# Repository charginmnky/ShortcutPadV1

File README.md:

# ShortcutPadV1
Shortcut PCB for desktop shortcuts like macros, muting, and volume controls.
## Pathfinder Session 1 - [40 minutes]
What I did:
I installed KiCad and Wakatime, and made my hackatime account.

Screenshot of progress:

## Pathfinder Session 2 - [40 minutes]
What I did:
I created my schematic, with 4 buttons and 4 leds.

Screenshot of progress:

## Pathfinder Session 3 - [2 hours 40 minutes]
What I did:
I added my footprints, and wired & designed my pcb.

Screenshot of progress:

## Pathfinder Session 4 - [20 minutes]
What I did:
I added 3d models of the parts to my code.

Screenshot of progress:

## Pathfinder Session 5 - [10 minutes]
What I did:
I started my code in arduino IDE.

Screenshot of progress:

## Pathfinder Session 6 - [30 minutes]
What I did:
I finished my code in arduino IDE.

Screenshot of progress:

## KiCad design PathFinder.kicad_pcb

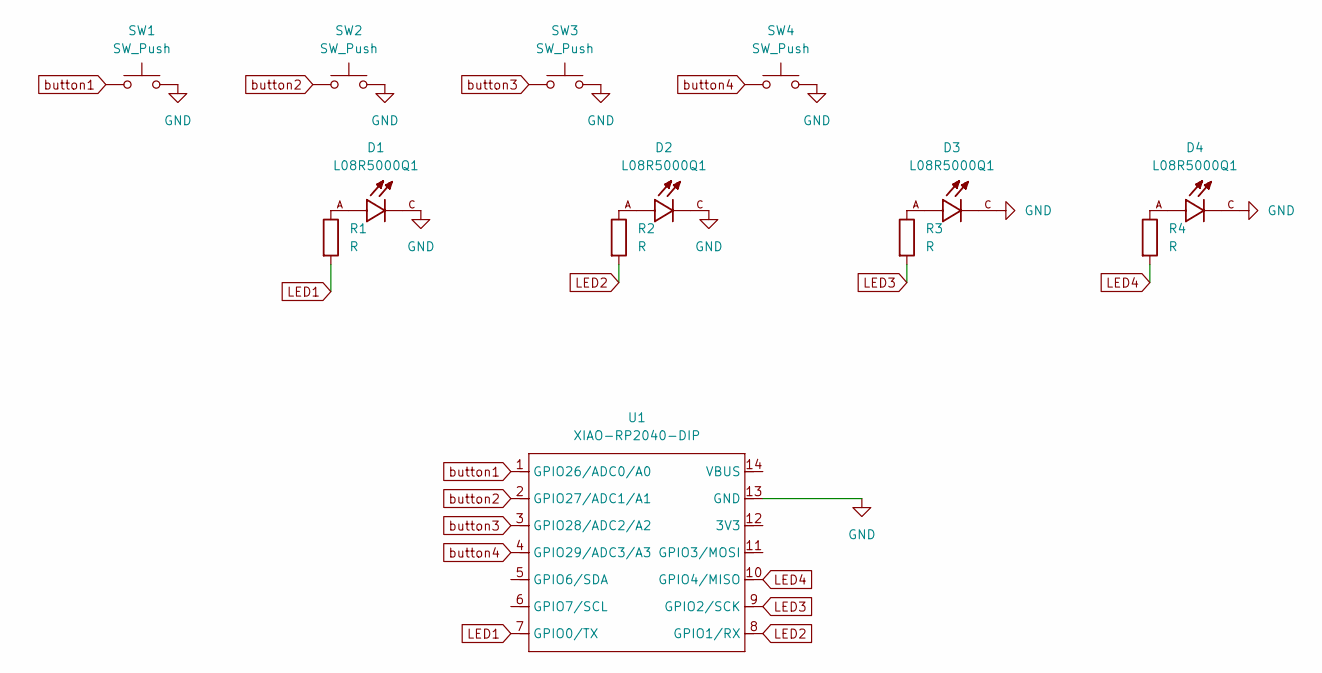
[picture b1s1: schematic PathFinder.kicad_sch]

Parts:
D1, D2, D3, D4: L08R5000Q1; LEDRD254W57D500H1070; PARTREV NA
R1, R2, R3, R4: R; R_Axial_DIN0204_L3.6mm_D1.6mm_P5.08mm_Horizontal
SW1, SW2, SW3, SW4: SW_Push; SW_Cherry_MX_1.00u_PCB
U1: XIAO-RP2040-DIP

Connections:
GND: D1.C, D2.C, D3.C, D4.C, SW1.2, SW2.2, SW3.2, SW4.2, U1.13 (GND)
LED1: R1.2, U1.7 (GPIO0/TX)
LED2: R2.2, U1.8 (GPIO1/RX)
LED3: R3.2, U1.9 (GPIO2/SCK)
LED4: R4.2, U1.10 (GPIO4/MISO)
unnamed: D1.A, R1.1
unnamed: D2.A, R2.1
unnamed: D3.A, R3.1
unnamed: D4.A, R4.1
button1: SW1.1, U1.1 (GPIO26/ADC0/A0)
button2: SW2.1, U1.2 (GPIO27/ADC1/A1)
button3: SW3.1, U1.3 (GPIO28/ADC2/A2)
button4: SW4.1, U1.4 (GPIO29/ADC3/A3)

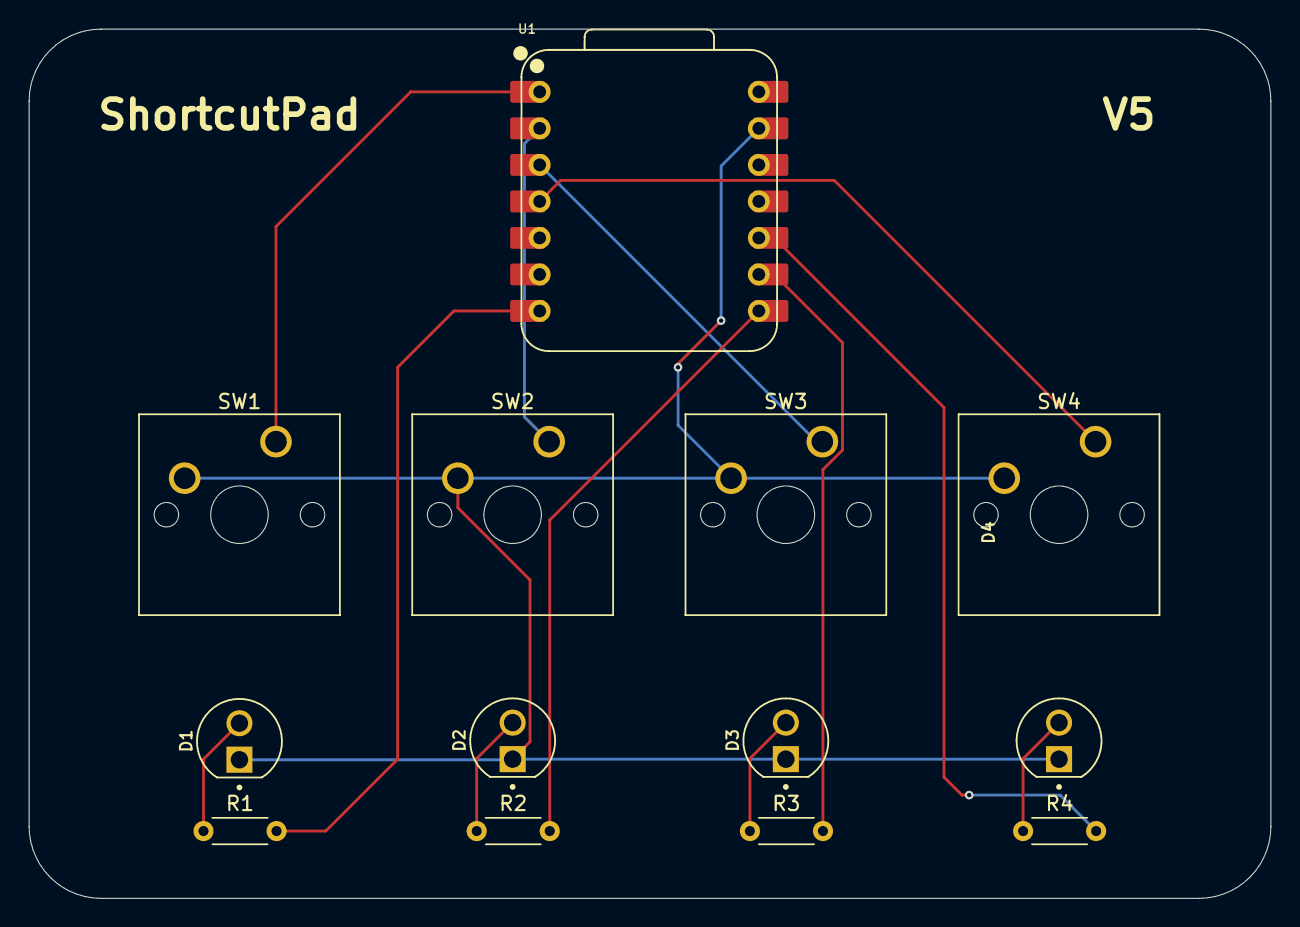
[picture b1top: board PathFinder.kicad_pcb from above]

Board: 2 copper layers, 86.4 x 60.5 mm, 13 parts (0 on the bottom side), 13 nets.

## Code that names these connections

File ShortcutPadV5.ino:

int BUT1 = DO;
int BUT2 = D1;
int BUT3 = D2;
int BUT4 = D3;

int LED1 = D6;
int LED2 = D7;
int LED3 = D8;
int LED4 = D9;

int currentLED = 0;

void setup()
{
pinMode(BUT1, INPUT_PULLUP);
pinMode(BUT2, INPUT_PULLUP);
pinMode(BUT3, INPUT_PULLUP);
pinMode(BUT4, INPUT_PULLUP);
  
pinMode(LED1, OUTPUT);
pinMode(LED2, OUTPUT);
pinMode(LED3, OUTPUT);
pinMode(LED4, OUTPUT);
  
randomSeed(analogRead(A0));

pickNewLED();
}

void loop()
{
if (currentLED == 0 && digitalRead(BUT1) == LOW) hit();
if (currentLED == 1 && digitalRead(BUT2) == LOW) hit();
if (currentLED == 2 && digitalRead(BUT3) == LOW) hit();
if (currentLED == 3 && digitalRead(BUT4) == LOW) hit();
}

void pickNewLED()
{
  digitalWrite(LED1, LOW);
  digitalWrite(LED2, LOW);
  digitalWrite(LED3, LOW);
  digitalWrite(LED4, LOW);

currentLED = random(0, 4);


if (currentLED == 0) digitalWrite(LED1, HIGH);
if (currentLED == 1) digitalWrite(LED2, HIGH);
if (currentLED == 2) digitalWrite(LED3, HIGH);
if (currentLED == 3) digitalWrite(LED4, HIGH);
}

void hit()
{
if (currentLED == 0) digitalWrite(LED1, LOW);
if (currentLED == 1) digitalWrite(LED2, LOW);
if (currentLED == 2) digitalWrite(LED3, LOW);
if (currentLED == 3) digitalWrite(LED4, LOW);

delay(150);
  
pickNewLED();
}
